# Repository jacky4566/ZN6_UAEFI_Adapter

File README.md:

# ZN6 ATLAS Adapter

A DIY adapter board that plugs the [FOME-tech](https://www.fome.tech) **ATLAS** ECU into the factory ECU connector of the **ZN6 platform** (Toyota 86 / Scion FR-S / Subaru BRZ, 2012–2020).

## What it does

The board has the same 135-pin ECU header as the factory ECU, so it plugs straight into the car's harness. Every ECU pin is mirrored to a labelled solder-pad field, and you connect the two with jumper wires.

That means you can wire up **any engine swap** on the factory body harness. You aren't locked into the FA20 pinout: route each harness pin to whatever ATLAS function your engine needs.

My own build is an **EZ36** (Subaru 3.6 L H6) swap. The pin plan for it is in the `H6 Tribeca` sheet of [`Wiring.xlsx`](Wiring.xlsx).

> **Status: REV A, untested.** Check the pinout against your own harness before powering anything.

## On-board extras

On top of the pass-through wiring, the adapter adds:

| Function | Part | Notes |
|---|---|---|
| Electronic throttle (ETB) | 2× Infineon TLE9201SG H-bridge | Two DC motor drivers (`DC Driver 1` / `DC Driver 2` sheets), controlled by `DCx_PWM`, `DCx_DIR` and `DCx_DIS`. Outputs on `OUT_DC1±` / `OUT_DC2±`. One drives the ETB, the second is free for another throttle, idle valve or wastegate. |
| VR conditioner | Maxim MAX9924 | Variable-reluctance crank/cam input (`VR1`) conditioned to a logic-level signal for the ATLAS. |
| IMU | ST LSM6DSV | 6-axis accelerometer + gyro on SPI (`SPI_SCK`, `SPI_MOSI`, `SPI_MISO`, `SPI_CS`, 3.3 V). |
| 4× low-side outputs | 2× ST VNLD5090 (dual) | Protected low-side switches on `LS9`–`LS12`, 3.5 A max, solenoid-load capable. |

Power is distributed on `12V_Constant`, `12V_SW` (key-on) and `12V_MR` (main relay), with fused feeds to the add-on circuits.

### ECU pin numbering

The factory ECU uses four connectors, which the TE 6376430-2 combines into one 135-position header. The pad numbers in the schematic map to the factory connector pins like this:

| Factory connector | Pins | Pad numbers |
|---|---|---|
| A (A33) | A1–A31 | 1–31 |
| B (A34) | B1–B35 | 32–66 |
| C (A35) | C1–C35 | 67–101 |
| D (A36) | D1–D34 | 102–135 |

For example, `B28` is pad 31 + 28 = **59**. The factory function of every pin is in the `BRZ FRS Pinout 2018` sheet of [`Wiring.xlsx`](Wiring.xlsx).

## Fixed pins

The following pins are hard-wired on the board.

| ECU pin | Pad | Factory function | Board net | Goes to |
|---|---|---|---|---|
| A1 | 1 | 12V From Main Relay | `12V_MR` | ATLAS 12V_MR |
| A2 | 2 | 12V Constant | `12V_Constant` | ATLAS 12V_Constant |
| A18 | 18 | CAN Lo | `CAN1-` | ATLAS CAN1 L |
| A19 | 19 | CAN Hi | `CAN1+` | ATLAS CAN1 H |
| A27 | 27 | 12V From IGN Switch | `12V_SW` | ATLAS 12V_IGN |
| A28 | 28 | Sensor ground (shield) | `GND` | Ground |
| B1 | 32 | Power ground | `GND` | Ground |
| B2 | 33 | Power ground | `GND` | Ground |
| B3 | 34 | Power ground | `GND` | Ground |
| B29 | 60 | Sensor ground (shield) | `GND` | Ground |
| B30 | 61 | Shield | `GND` | Ground |
| B35 | 66 | Sensor ground (shield) | `GND` | Ground |
| C7 | 73 | ETCS Relay Output | `ETCS` | ETB Driver chips |
| D3 | 104 | Power ground | `GND` | Ground |
| D4 | 105 | Power ground | `GND` | Ground |

The factory CAN bus on A18/A19 (the "CAN2" in Toyota's naming) is wired to the ATLAS CAN1.

## Revisions
REV A
- I assume this board is perfect and will never need updating....Hopefully..

## Libraries

The ATLAS module footprint and symbols come from the [FOME libraries](FOME-libraries-main/) (`fome_modules`). Project-specific symbols and footprints are in `ZN6_Adapter.kicad_sym` and `ZN6.pretty`.

## References

- [FT86Club ECU pinout thread](https://www.ft86club.com/forums/showthread.php?t=143079)
- [TE 6376430-2 connector](https://www.digikey.com/en/products/detail/te-connectivity-amp-connectors/6376430-2/18111199)
- [TLE9201SG](https://www.infineon.com/cms/en/product/power/motor-control-ics/brushed-dc-motor-driver-ics/single-half-bridge-full-bridge-motor-driver-ics/tle9201sg/), [MAX9924](https://www.analog.com/en/products/max9924.html), [LSM6DSV](https://www.st.com/en/mems-and-sensors/lsm6dsv.html), [VNLD5090](https://www.st.com/en/automotive-analog-and-power/vnld5090-e.html)

## License

[MIT](LICENSE) © 2026 Jacky4566

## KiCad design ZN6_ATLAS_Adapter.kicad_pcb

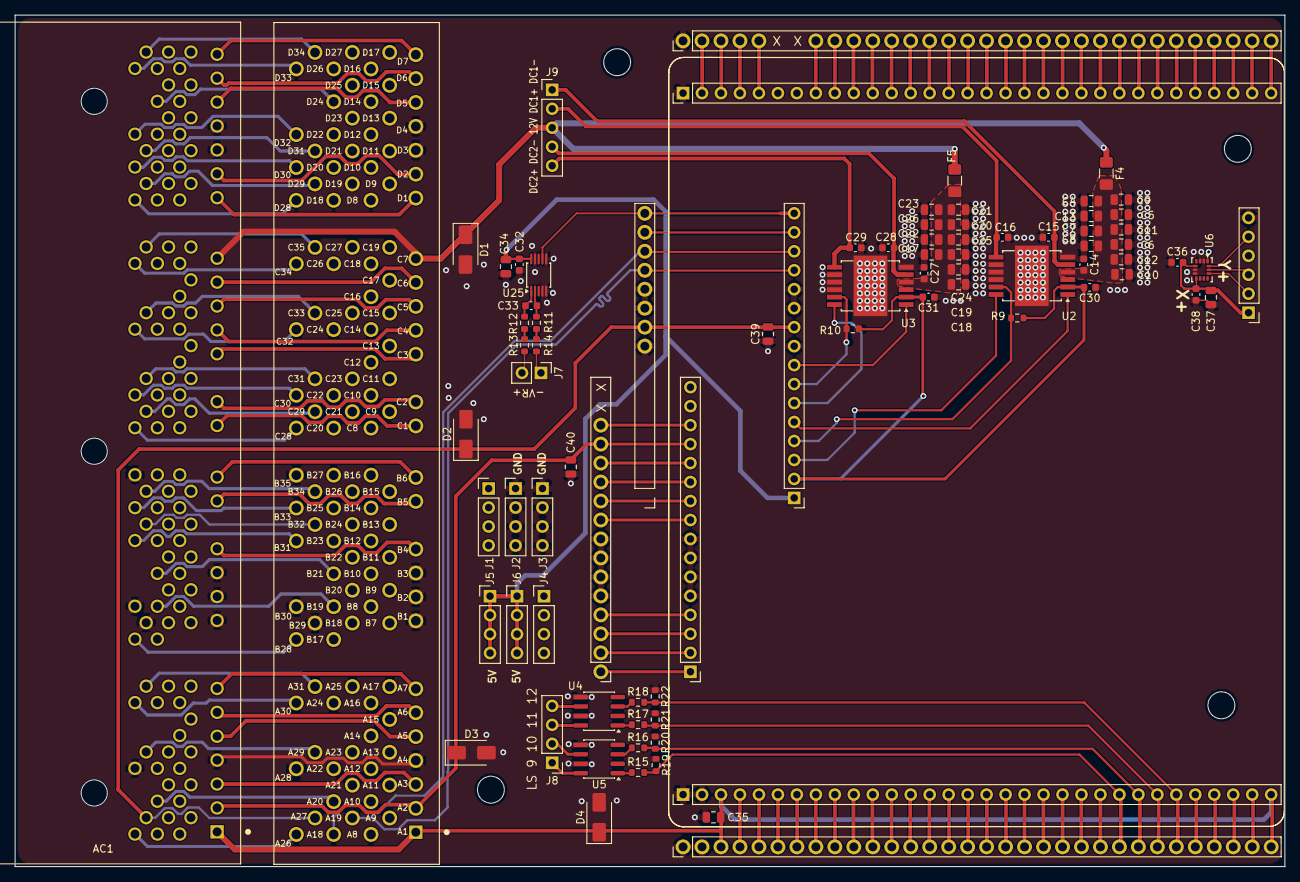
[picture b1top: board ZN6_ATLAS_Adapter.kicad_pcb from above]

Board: 4 copper layers, 170.0 x 114.0 mm, 76 parts (0 on the bottom side), 228 nets.

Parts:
AC1, AC2: 6376430-2; TE_6376430-2
C4, C5, C6, C7, C8, C9, C10, C11, C12, C13, C17, C18, C19, C20, C21, C22, C23, C24, C25, C26, C34, C35, C37, C39, C40: 10u; C_0805_2012Metric
C14, C27, C30, C31, C32, C36, C38: 100n; C_0603_1608Metric
C15, C16, C28, C29: 10n; C_0603_1608Metric
C33: 1n; C_0603_1608Metric
D1, D2, D3, D4: SMAJ36A; D_SMA
F4, F5: Fuse; Fuse_1206_3216Metric_Pad1.42x1.75mm_HandSolder
J1, J2, J3, J4, J5, J6, J8: Conn_01x04_Socket; PinHeader_1x04_P2.54mm_Vertical
J7: Conn_01x02_Socket; PinHeader_1x02_P2.54mm_Vertical
J9: Conn_01x05_Pin; PinHeader_1x05_P2.54mm_Vertical
M1, M2: Polygonus ECU Module; polygonus
R9, R10, R11, R12, R13, R14, R15, R16, R17, R18, R19, R20, R21, R22: 10k; R_0603_1608Metric
U2, U3: TLE9201SG; Infineon_PG-DSO-12-11
U4, U5: VNLD5090; SOIC-8_3.9x4.9mm_P1.27mm
U6: LSM6DSV; LGA-14_3x2.5mm_P0.5mm_LayoutBorder3x4y
U25: MAX9924; TSSOP-10_3x3mm_P0.5mm

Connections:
+3.3V: C30.2, C31.2, M1.82 (3V3), R9.2, R10.2, U2.2 (VSO), U3.2 (VSO)
+5V: C32.2, C34.2, J5.1, J5.2, J5.3, J5.4, J6.1, J6.2, J6.3, J6.4, M1.81 (5V), U25.10 (VCC)
/12V_Constant: AC1.2, AC2.2, C40.2, D3.1 (K), M1.77, M2.77
/12V_MR: AC1.1, AC2.1, C35.2, D4.1 (K), M1.3 (12V_MR), M1.32 (12V_MR), M2.3 (12V_MR), M2.32 (12V_MR)
/12V_SW: AC1.27, AC2.27, C39.2, D2.1 (K), M1.90 (12V_IGN), M2.90 (12V_IGN)
/CAN1+: AC1.19, AC2.19, M1.93 (CAN+), M2.93 (CAN+)
/CAN1-: AC1.18, AC2.18, M1.94 (CAN-), M2.94 (CAN-)
/DC1_DIR: M1.85 (ETB1_DIR), U2.1 (DIR)
/DC1_DIS: M1.84 (ETB1_DIS), R9.1, U2.11 (DIS)
/DC1_PWM: M1.83 (ETB1_PWM), U2.12 (PWM)
/DC2_DIR: M1.88 (ETB2_DIR), U3.1 (DIR)
/DC2_DIS: M1.87 (ETB2_DIS), R10.1, U3.11 (DIS)
/DC2_PWM: M1.86 (ETB2_PWM), U3.12 (PWM)
/DC Driver 1/PWR: C4.2, C5.2, C6.2, C7.2, C8.2, C9.2, C10.2, C11.2, C12.2, C13.2, C14.2, F4.2, U2.4 (VS)
/DC Driver 2/PWR: C17.2, C18.2, C19.2, C20.2, C21.2, C22.2, C23.2, C24.2, C25.2, C26.2, C27.2, F5.2, U3.4 (VS)
/ETCS: AC1.73, AC2.73, D1.1 (K), F4.1, F5.1, J9.3
/IGN10: M1.14 (IGN10), M2.14 (IGN10)
/IGN11: M1.13 (IGN11), M2.13 (IGN11)
/IGN12: M1.12 (IGN12), M2.12 (IGN12)
/KNOCK1: M1.63 (Knock_1), M2.63 (Knock_1)
/KNOCK2: M1.64 (Knock_2), M2.64 (Knock_2)
/LS1: M1.4 (LS1), M2.4 (LS1)
/LS2: M1.5 (LS2), M2.5 (LS2)
/LS3: M1.6 (LS3), M2.6 (LS3)
/LS4: M1.7 (LS4), M2.7 (LS4)
/LS5: M1.8 (LS5), M2.8 (LS5)
/LS6: M1.9 (LS6), M2.9 (LS6)
/LS7: M1.10 (LS7), M2.10 (LS7)
/LS8: M1.11 (LS8), M2.11 (LS8)
/LS9: M1.24, M2.24, R15.2, R19.1
/LS10: M1.25, M2.25, R16.2, R20.1
/LS11: M1.26, M2.26, R17.2, R21.1
/LS12: M1.27, M2.27, R18.2, R22.1
/MAX9924+: J7.2, R13.2
/MAX9924-: J7.1, R14.2
/OUT_DC1+: C16.2, J9.2, U2.7 (OUT2)
/OUT_DC1-: C15.2, J9.1, U2.5 (OUT1)
/OUT_DC2+: C29.2, J9.5, U3.7 (OUT2)
/OUT_DC2-: C28.2, J9.4, U3.5 (OUT1)
/RC1: M1.75 (RC1), M2.75 (RC1)
/RC2: M1.76 (RC2), M2.76 (RC2)
/SPI_3V3: C36.2, C37.2, C38.2, M1.102, U6.5 (VDDIO), U6.8 (VDD)
/SPI_CS: M1.103, U6.12 (CS)
/SPI_MISO: M1.105, U6.1 (SDO/SA0)
/SPI_MOSI: M1.106, U6.14 (SDA)
/SPI_SCK: M1.104, U6.13 (SCL)
/VR1: M1.96 (VR1), M2.96 (VR1), U25.7 (COUT)
/VR2: M1.95 (VR2), M2.95 (VR2)
GND: AC1.28, AC1.32, AC1.33, AC1.34, AC1.60, AC1.61, AC1.66, AC1.104, AC1.105, AC2.28, AC2.32, AC2.33, AC2.34, AC2.60, AC2.61, AC2.66, AC2.104, AC2.105, C4.1, C5.1, C6.1, C7.1, C8.1, C9.1, C10.1, C11.1, C12.1, C13.1, C14.1, C15.1, C16.1, C17.1, C18.1, C19.1, C20.1, C21.1, C22.1, C23.1, C24.1, C25.1, C26.1, C27.1, C28.1, C29.1, C30.1, C31.1, C32.1, C34.1, C35.1, C36.1, C37.1, C38.1, C39.1, C40.1, D1.2 (A), D2.2 (A), D3.2 (A), D4.2 (A), J2.1, J2.2, J2.3, J2.4, J3.1, J3.2, J3.3, J3.4, M1.1 (GND), M1.2 (GND), M1.33 (GND), M1.69 (GND), M1.70 (GND), M1.71 (GND), M1.72 (GND), M1.89 (GND), M1.91 (GND), M1.92 (GND), M1.107, M2.1 (GND), M2.2 (GND), M2.33 (GND), M2.69 (GND), M2.70 (GND), M2.71 (GND), M2.72 (GND), M2.89 (GND), M2.91 (GND), M2.92 (GND), R19.2, R20.2, R21.2, R22.2, U2.6 (GND), U2.8 (SI), U2.9 (CSN), U2.10 (SCK), U2.13 (GND), U3.6 (GND), U3.8 (SI), U3.9 (CSN), U3.10 (SCK), U3.13 (GND), U4.5 (S2), U4.7 (S1), U5.5 (S2), U5.7 (S1), U6.2 (SDX), U6.3 (SCX), U6.6 (GND), U6.7 (GND), U25.4 (BIAS), U25.5 (GND), U25.6 (ZERO_EN), U25.9 (INT_THRS)
unnamed: AC1.3, AC2.3
unnamed: AC1.4, AC2.4
unnamed: AC1.5, AC2.5
unnamed: AC1.6, AC2.6
unnamed: AC1.7, AC2.7
unnamed: AC1.8, AC2.8
unnamed: AC1.9, AC2.9
unnamed: AC1.10, AC2.10
unnamed: AC1.11, AC2.11
unnamed: AC1.12, AC2.12
unnamed: AC1.13, AC2.13
unnamed: AC1.14, AC2.14
unnamed: AC1.15, AC2.15
unnamed: AC1.16, AC2.16
unnamed: AC1.17, AC2.17
unnamed: AC1.20, AC2.20
unnamed: AC1.21, AC2.21
unnamed: AC1.22, AC2.22
unnamed: AC1.23, AC2.23
unnamed: AC1.24, AC2.24
unnamed: AC1.25, AC2.25
unnamed: AC1.26, AC2.26
unnamed: AC1.29, AC2.29
unnamed: AC1.30, AC2.30
unnamed: AC1.31, AC2.31
unnamed: AC1.35, AC2.35
unnamed: AC1.36, AC2.36
unnamed: AC1.37, AC2.37
unnamed: AC1.38, AC2.38
unnamed: AC1.39, AC2.39
unnamed: AC1.40, AC2.40
unnamed: AC1.41, AC2.41
unnamed: AC1.42, AC2.42
unnamed: AC1.43, AC2.43
unnamed: AC1.44, AC2.44
unnamed: AC1.45, AC2.45
unnamed: AC1.46, AC2.46
unnamed: AC1.47, AC2.47
unnamed: AC1.48, AC2.48
unnamed: AC1.49, AC2.49
unnamed: AC1.50, AC2.50
unnamed: AC1.51, AC2.51
unnamed: AC1.52, AC2.52
unnamed: AC1.53, AC2.53
unnamed: AC1.54, AC2.54
unnamed: AC1.55, AC2.55
unnamed: AC1.56, AC2.56
unnamed: AC1.57, AC2.57
unnamed: AC1.58, AC2.58
unnamed: AC1.59, AC2.59
unnamed: AC1.62, AC2.62
unnamed: AC1.63, AC2.63
unnamed: AC1.64, AC2.64
unnamed: AC1.65, AC2.65
unnamed: AC1.67, AC2.67
unnamed: AC1.68, AC2.68
unnamed: AC1.69, AC2.69
unnamed: AC1.70, AC2.70
unnamed: AC1.71, AC2.71
unnamed: AC1.72, AC2.72
unnamed: AC1.74, AC2.74
unnamed: AC1.75, AC2.75
unnamed: AC1.76, AC2.76
unnamed: AC1.77, AC2.77
unnamed: AC1.78, AC2.78
unnamed: AC1.79, AC2.79
unnamed: AC1.80, AC2.80
unnamed: AC1.81, AC2.81
unnamed: AC1.82, AC2.82
unnamed: AC1.83, AC2.83
unnamed: AC1.84, AC2.84
unnamed: AC1.85, AC2.85
unnamed: AC1.86, AC2.86
unnamed: AC1.87, AC2.87
unnamed: AC1.88, AC2.88
unnamed: AC1.89, AC2.89
unnamed: AC1.90, AC2.90
unnamed: AC1.91, AC2.91
unnamed: AC1.92, AC2.92
unnamed: AC1.93, AC2.93
unnamed: AC1.94, AC2.94
unnamed: AC1.95, AC2.95
unnamed: AC1.96, AC2.96
unnamed: AC1.97, AC2.97
unnamed: AC1.98, AC2.98
unnamed: AC1.99, AC2.99
unnamed: AC1.100, AC2.100
unnamed: AC1.101, AC2.101
unnamed: AC1.102, AC2.102
unnamed: AC1.103, AC2.103
unnamed: AC1.106, AC2.106
unnamed: AC1.107, AC2.107
unnamed: AC1.108, AC2.108
unnamed: AC1.109, AC2.109
unnamed: AC1.110, AC2.110
unnamed: AC1.111, AC2.111
unnamed: AC1.112, AC2.112
unnamed: AC1.113, AC2.113
unnamed: AC1.114, AC2.114
unnamed: AC1.115, AC2.115
unnamed: AC1.116, AC2.116
unnamed: AC1.117, AC2.117
unnamed: AC1.118, AC2.118
unnamed: AC1.119, AC2.119
unnamed: AC1.120, AC2.120
unnamed: AC1.121, AC2.121
unnamed: AC1.122, AC2.122
unnamed: AC1.123, AC2.123
unnamed: AC1.124, AC2.124
unnamed: AC1.125, AC2.125
unnamed: AC1.126, AC2.126
unnamed: AC1.127, AC2.127
unnamed: AC1.128, AC2.128
unnamed: AC1.129, AC2.129
unnamed: AC1.130, AC2.130
unnamed: AC1.131, AC2.131
unnamed: AC1.132, AC2.132
unnamed: AC1.133, AC2.133
unnamed: AC1.134, AC2.134
unnamed: AC1.135, AC2.135
unnamed: J8.1, U5.8 (D1)
unnamed: J8.2, U5.6 (D2)
unnamed: J8.3, U4.8 (D1)
unnamed: J8.4, U4.6 (D2)
unnamed: M1.40 (5V_SENSOR_1), M2.40 (5V_SENSOR_1)
unnamed: M1.41 (5V_SENSOR_1), M2.41 (5V_SENSOR_1)
unnamed: M1.36 (5V_SENSOR_2), M2.36 (5V_SENSOR_2)
unnamed: M1.37 (5V_SENSOR_2), M2.37 (5V_SENSOR_2)
unnamed: M1.73 (CAN2+), M2.73 (CAN2+)
unnamed: M1.74 (CAN2-), M2.74 (CAN2-)
unnamed: M1.15, M2.15
unnamed: M1.16, M2.16
unnamed: M1.17, M2.17
unnamed: M1.18, M2.18
unnamed: M1.19, M2.19
unnamed: M1.20, M2.20
unnamed: M1.21, M2.21
unnamed: M1.22, M2.22
unnamed: M1.23, M2.23
unnamed: M1.28, M2.28
unnamed: M1.29, M2.29
unnamed: M1.30, M2.30
unnamed: M1.31, M2.31
unnamed: M1.34, M2.34
unnamed: M1.35, M2.35
unnamed: M1.42, M2.42
unnamed: M1.43, M2.43
unnamed: M1.44, M2.44
unnamed: M1.45, M2.45
unnamed: M1.46, M2.46
unnamed: M1.47, M2.47
unnamed: M1.48, M2.48
unnamed: M1.49, M2.49
unnamed: M1.50, M2.50
unnamed: M1.51, M2.51
unnamed: M1.52, M2.52
unnamed: M1.53, M2.53
unnamed: M1.54, M2.54
unnamed: M1.55, M2.55
unnamed: M1.56, M2.56
unnamed: M1.57, M2.57
unnamed: M1.58, M2.58
unnamed: M1.59, M2.59
unnamed: M1.60, M2.60
unnamed: M1.61, M2.61
unnamed: M1.62, M2.62
unnamed: M1.65, M2.65
unnamed: M1.66, M2.66
unnamed: M1.67, M2.67
unnamed: M1.68, M2.68
unnamed: M1.78, M2.78
unnamed: R11.2, R14.1
unnamed: R12.2, R13.1
unnamed: R17.1, U4.1 (IN1)
unnamed: R18.1, U4.3 (IN2)
unnamed: R15.1, U5.1 (IN1)
unnamed: R16.1, U5.3 (IN2)
unnamed: C33.1, R12.1, U25.1 (IN+)
unnamed: C33.2, R11.1, U25.2 (IN-)
